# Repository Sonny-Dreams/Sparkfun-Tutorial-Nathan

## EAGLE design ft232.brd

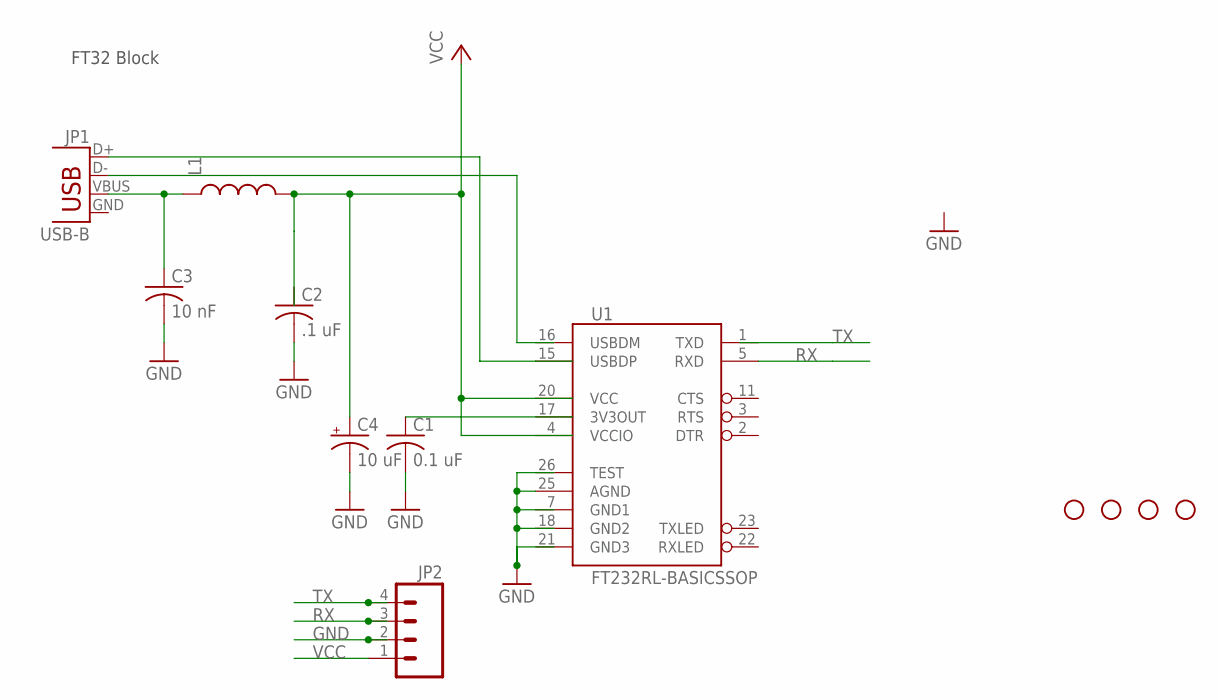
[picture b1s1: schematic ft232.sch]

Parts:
C1: 0.1 uF; C0603
C2: .1 uF; C0603
C3: 10 nF; C0603
C4: 10 uF; EIA3216
JP1: USB-B; USB-B-PTH
JP2: M04PTH; 1X04
L1: INDUCTOR0603; 0603
STANDOFF1, STANDOFF2, STANDOFF3, STANDOFF4: STAND-OFF
U1: FT232RL-BASICSSOP; SSOP28DB

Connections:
GND: C1.2, C2.2, C3.2, C4.C (-), JP2.2, U1.25 (AGND)
GND1: U1.7 (GND1)
GND2: U1.18 (GND2)
GND3: U1.21 (GND3)
unnamed: C3.1, JP1.VBUS, L1.1
RX: JP2.3, U1.5 (RXD)
TX: JP2.4
VCC: C4.A (+), JP2.1, L1.2, U1.20 (VCC)
VCCIO: U1.4 (VCCIO)

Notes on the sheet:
FT32 Block

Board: 2 copper layers, 12 parts (0 on the bottom side), 4 nets, no tracks yet.

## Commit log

2015-09-30 :space_invader: Added .gitattributes & .gitignore files
2015-09-30 try
    commit me

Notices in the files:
parts and their libraries:
SparkFun-Passives: Licensing: Creative Commons ShareAlike 4.0 International - https://creativecommons.org/licenses/by-sa/4.0
